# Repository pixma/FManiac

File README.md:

FManiac
=======

A simple fm radio small sized gadget, runs on li-ion battery.

-------------------------------------------

### Has features
- FM radio module.
- LCD screen.
- Capacitive touch sensor button.
- Li-ion battery support.
- Battery charging.
- 4 pin audio jack/ 3.5mm audio jack audio output.

### FM radio module
- TEA5767 FM Radio Module

### LCD screen
- nokia 5110 lcd screen.

### MCU selection
- atmega328

### Capacitive touch sensor switch
- will be on baord.

### Li ion battery support
- tp4056

### audio jack
- 3.5 mm jack or 4 slot audio jack (selection left.)

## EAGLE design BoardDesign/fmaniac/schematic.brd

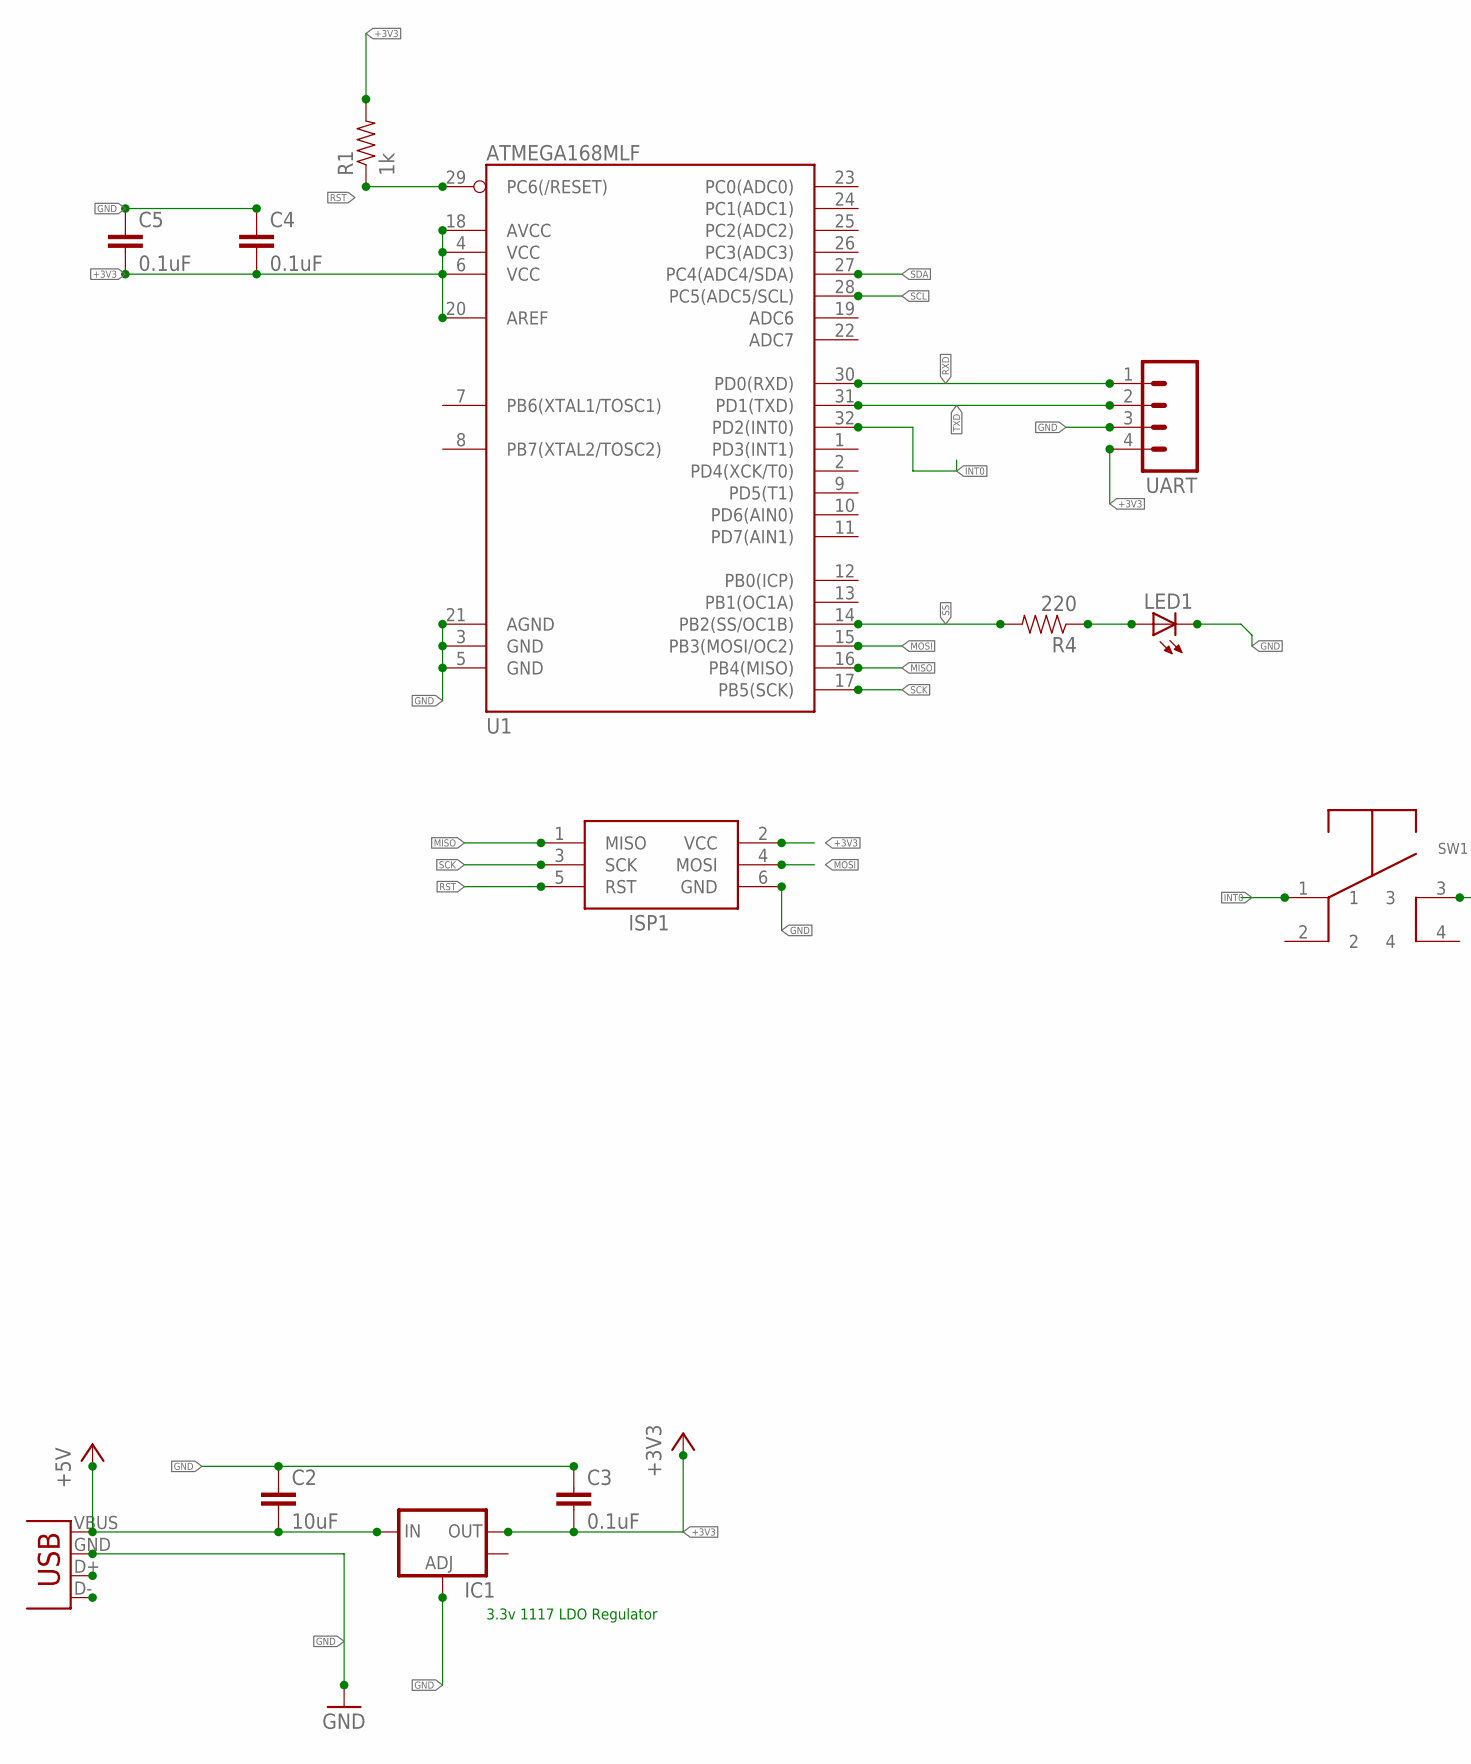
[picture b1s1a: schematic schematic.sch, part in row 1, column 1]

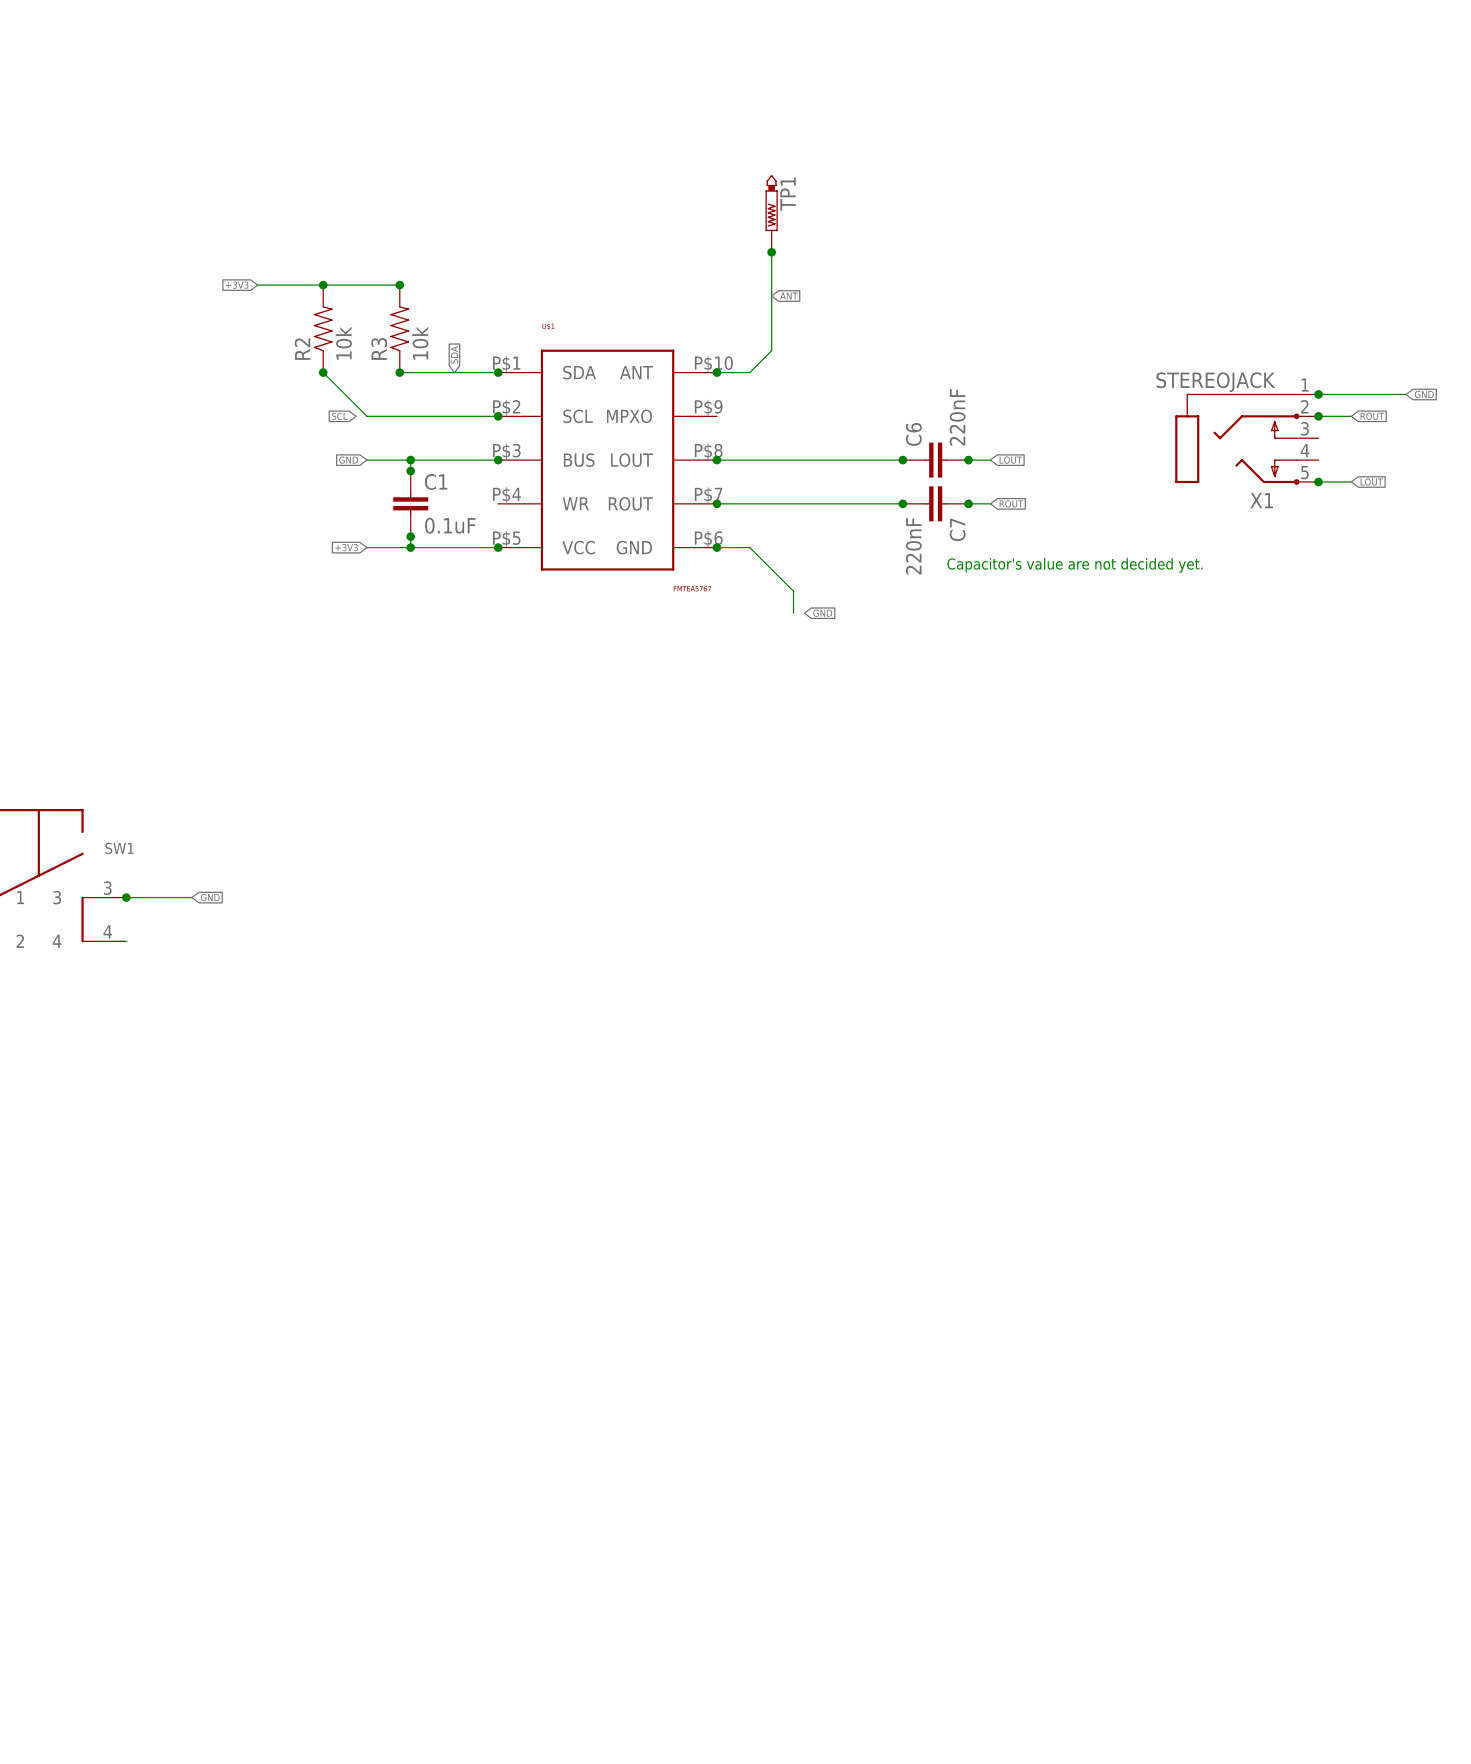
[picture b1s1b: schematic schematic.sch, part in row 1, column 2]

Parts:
C1, C3, C4, C5: 0.1uF; 0402-CAP
C2: 10uF; 0402-CAP
C6, C7: 220nF; 0402-CAP
IC1: V_REG_LM1117SOT223; SOT223
ISP1: AVRISP-6; AVRISP
JP1: USB-A-H
LED1: LEDCHIPLED_0603; CHIPLED_0603
R1: 1k; 0402-RES
R2, R3: 10k; 0402-RES
R4: 220; 0402-RES
SW1: TAC-SOFT; SWITCH_SMD
TP1: PTR1TP20SQ; TP20SQ
U1: ATMEGA168MLF; MLF32
U$1: FMTEA5767
UART: M04PTH; 1X04
X1: STEREOJACK; STX3100

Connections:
+3V3: C1.2, C3.2, C4.2, C5.2, IC1.2 (OUT), ISP1.2 (VCC), R1.2, R2.2, R3.2, U1.4 (VCC), U1.6 (VCC), U1.18 (AVCC), U1.20 (AREF), U$1.P$5 (VCC), UART.4
+5V: C2.2, IC1.3 (IN), JP1.VBUS (GND)
ANT: TP1.TP, U$1.P$10 (ANT)
GND: C1.1, C2.1, C3.1, C4.1, C5.1, IC1.1 (ADJ), ISP1.6 (GND), JP1.GND (VBUS), LED1.C, SW1.3, U1.3 (GND), U1.5 (GND), U1.21 (AGND), U$1.P$3 (BUS), U$1.P$6 (GND), UART.3, X1.1
INT0: SW1.1, U1.32 (PD2(INT0))
LOUT: C6.2, X1.5
MISO: ISP1.1 (MISO), U1.16 (PB4(MISO))
MOSI: ISP1.4 (MOSI), U1.15 (PB3(MOSI/OC2))
unnamed: C6.1, U$1.P$8 (LOUT)
unnamed: LED1.A, R4.1
unnamed: C7.2, U$1.P$7 (ROUT)
ROUT: C7.1, X1.2
RST: ISP1.5 (RST), R1.1, U1.29 (PC6(/RESET))
RXD: U1.30 (PD0(RXD)), UART.1
SCK: ISP1.3 (SCK), U1.17 (PB5(SCK))
SCL: R2.1, U1.28 (PC5(ADC5/SCL)), U$1.P$2 (SCL)
SDA: R3.1, U1.27 (PC4(ADC4/SDA)), U$1.P$1 (SDA)
SS: R4.2, U1.14 (PB2(SS/OC1B))
TXD: U1.31 (PD1(TXD)), UART.2

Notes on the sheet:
Capacitor's value are not decided yet.
3.3v 1117 LDO Regulator

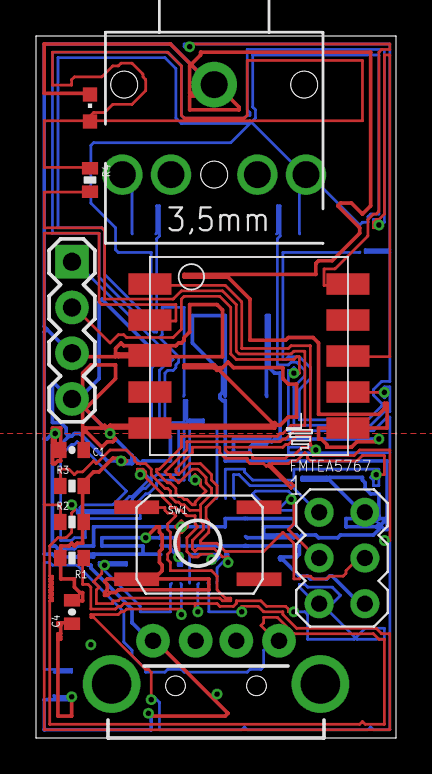
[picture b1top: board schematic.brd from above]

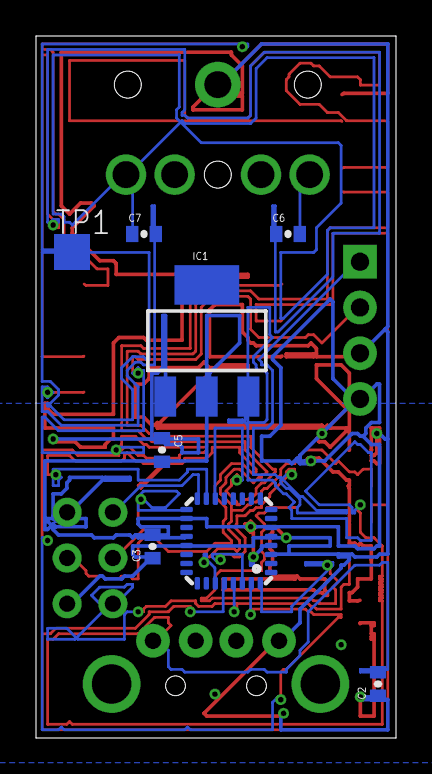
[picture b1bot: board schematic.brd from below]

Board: 2 copper layers, 20.0 x 39.0 mm, 21 parts (8 on the bottom side), 19 nets.

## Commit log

2014-07-15 normal push
2014-07-16 initial commits.
2014-08-10 Normal Push, Interrupt Button Added.

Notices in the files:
parts and their libraries:
SparkFun-DigitalIC: Licensing: Creative Commons ShareAlike 4.0 International - https://creativecommons.org/licenses/by-sa/4.0
